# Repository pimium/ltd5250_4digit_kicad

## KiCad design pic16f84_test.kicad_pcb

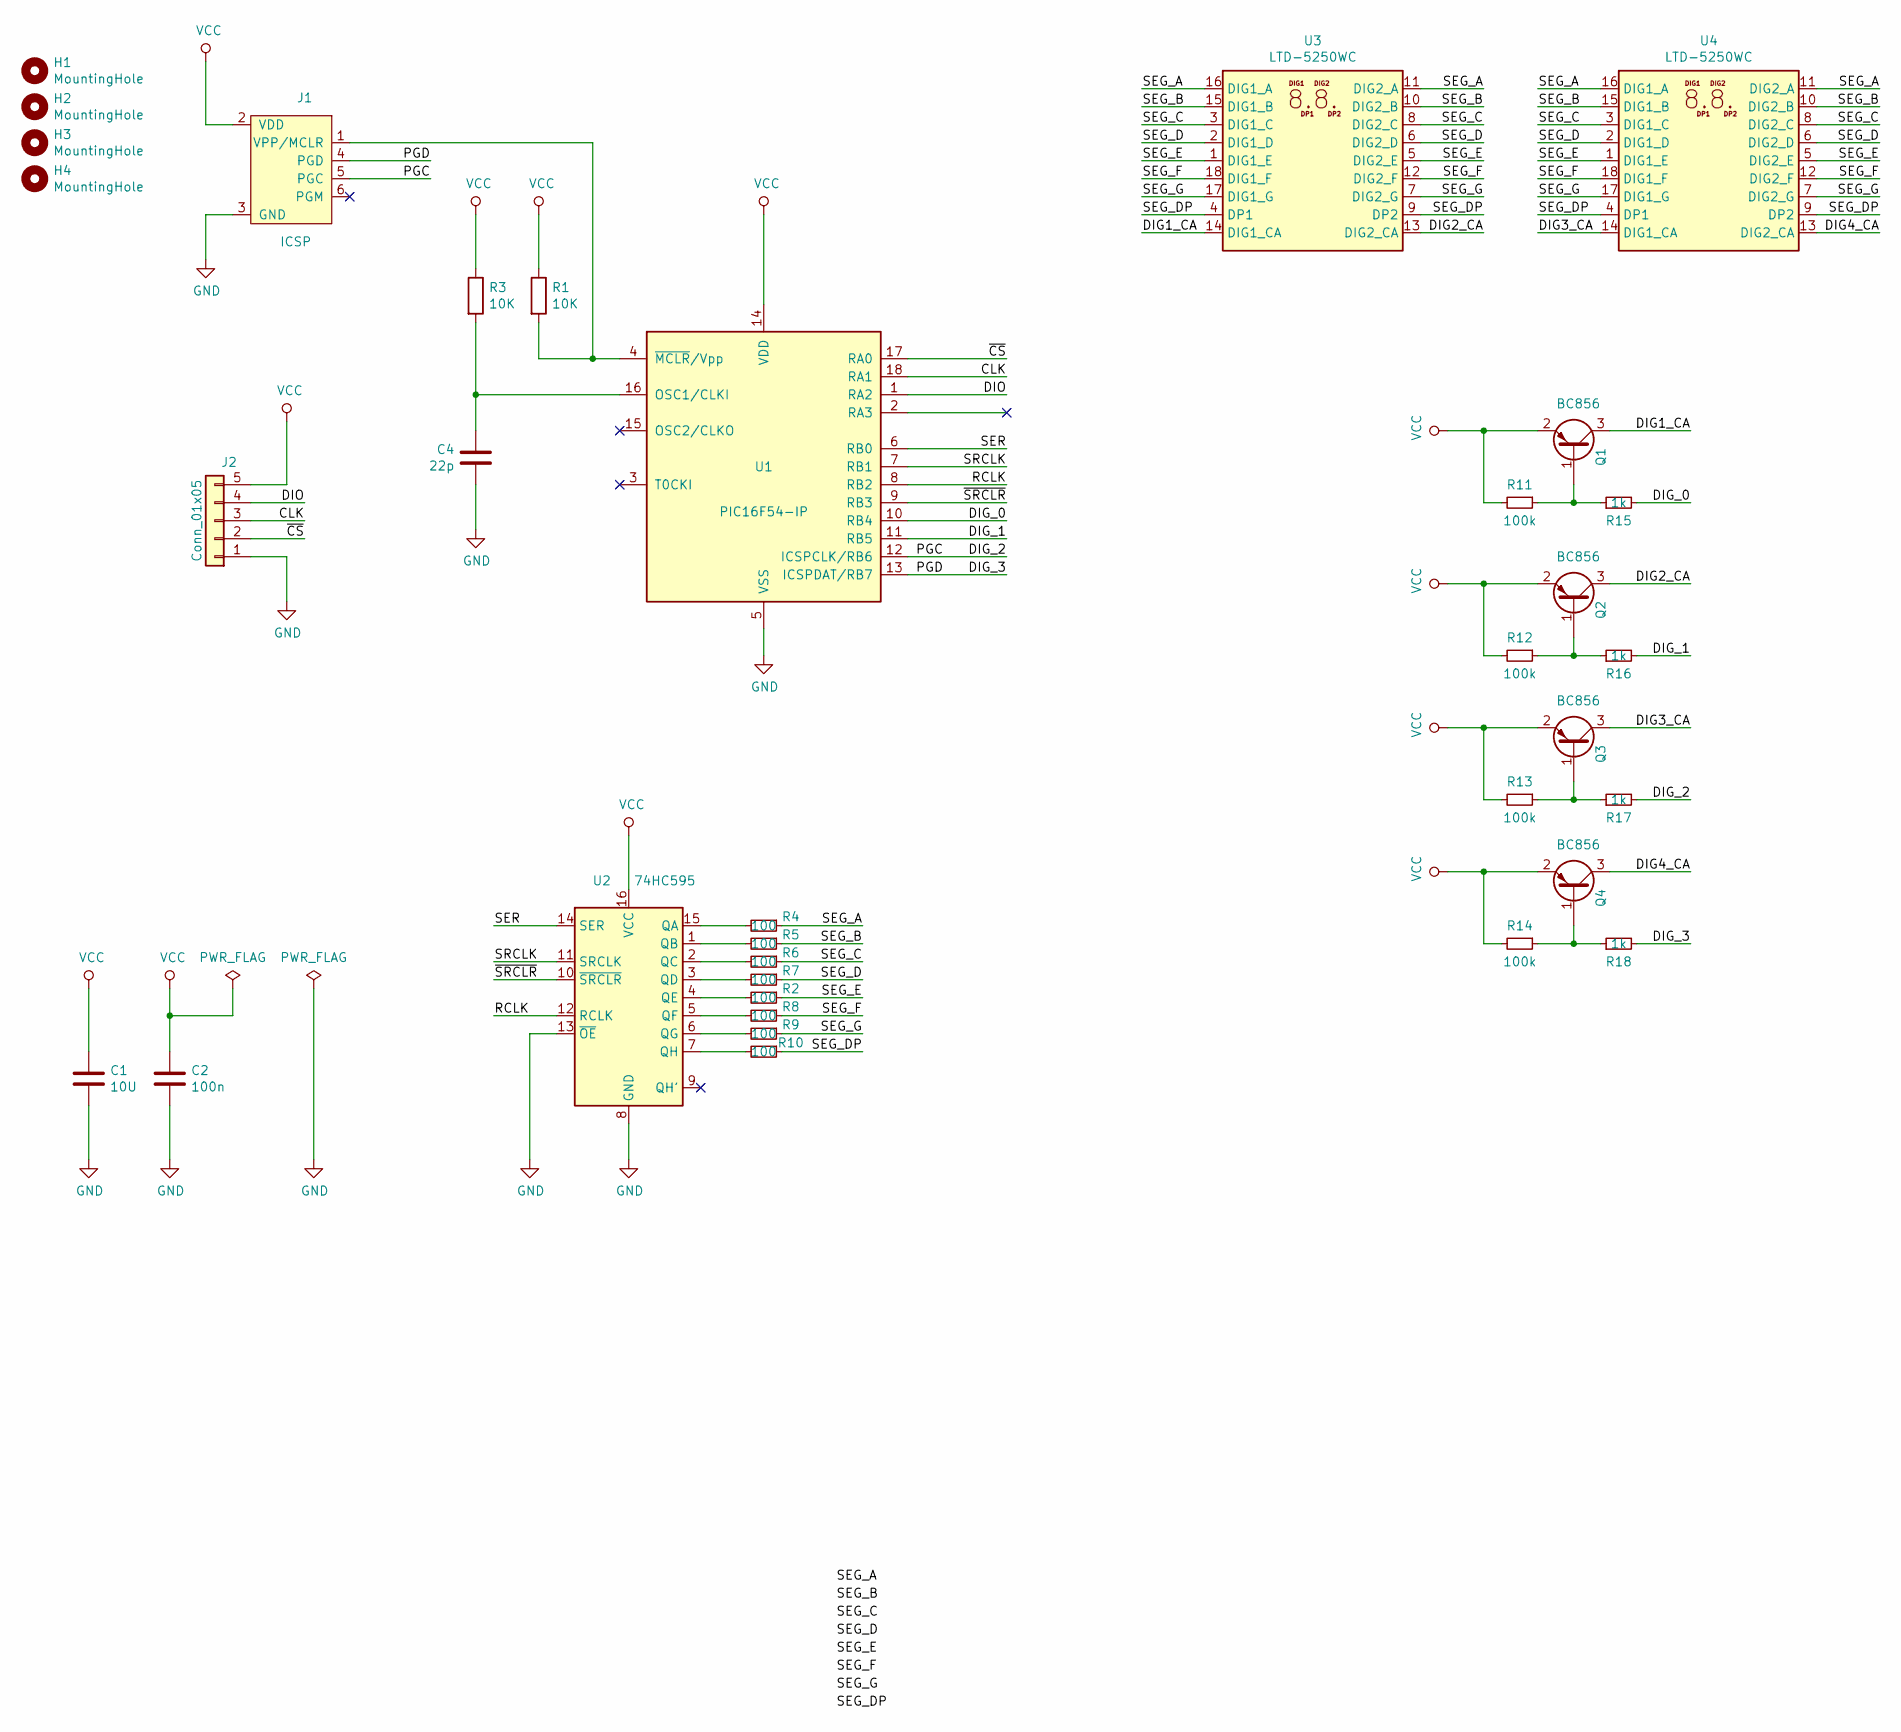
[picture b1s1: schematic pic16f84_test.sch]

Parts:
C1: 10U; C_0805_2012Metric_Pad1.15x1.40mm_HandSolder
C2: 100n; C_0805_2012Metric_Pad1.15x1.40mm_HandSolder
C4: 22p; C_0805_2012Metric_Pad1.15x1.40mm_HandSolder
H1, H2, H3, H4: MountingHole; MountingHole_3.2mm_M2
J1: ICSP; PinHeader_1x06_P2.54mm_Vertical
J2: Conn_01x05; PinHeader_1x05_P2.54mm_Vertical
Q1, Q2, Q3, Q4: BC856; SOT-23
R1, R3: 10K; R_0603_1608Metric_Pad1.05x0.95mm_HandSolder
R2, R4, R5, R6, R7, R8, R9, R10: 100; R_0603_1608Metric_Pad1.05x0.95mm_HandSolder
R11, R12, R13, R14: 100k; R_0603_1608Metric_Pad1.05x0.95mm_HandSolder
R15, R16, R17, R18: 1k; R_0603_1608Metric_Pad1.05x0.95mm_HandSolder
U1: PIC16F54-IP; SOP-18_7.0x12.5mm_P1.27mm
U2: 74HC595; SOIC-16_3.9x9.9mm_P1.27mm
U3, U4: LTD-5250WC; DA56-11CGKWA

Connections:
/CLK: J2.3, U1.18 (RA1)
/DIG1_CA: Q1.3 (C), U3.14 (DIG1_CA)
/DIG2_CA: Q2.3 (C), U3.13 (DIG2_CA)
/DIG3_CA: Q3.3 (C), U4.14 (DIG1_CA)
/DIG4_CA: Q4.3 (C), U4.13 (DIG2_CA)
/DIG_0: R15.2, U1.10 (RB4)
/DIG_1: R16.2, U1.11 (RB5)
/DIG_2: J1.5 (PGC), R17.2, U1.12 (ICSPCLK/RB6)
/DIG_3: J1.4 (PGD), R18.2, U1.13 (ICSPDAT/RB7)
/DIO: J2.4, U1.1 (RA2)
/RCLK: U1.8 (RB2), U2.12 (RCLK)
/SEG_A: R4.1, U3.11 (DIG2_A), U3.16 (DIG1_A), U4.11 (DIG2_A), U4.16 (DIG1_A)
/SEG_B: R5.1, U3.10 (DIG2_B), U3.15 (DIG1_B), U4.10 (DIG2_B), U4.15 (DIG1_B)
/SEG_C: R6.1, U3.3 (DIG1_C), U3.8 (DIG2_C), U4.3 (DIG1_C), U4.8 (DIG2_C)
/SEG_D: R7.1, U3.2 (DIG1_D), U3.6 (DIG2_D), U4.2 (DIG1_D), U4.6 (DIG2_D)
/SEG_DP: R10.1, U3.4 (DP1), U3.9 (DP2), U4.4 (DP1), U4.9 (DP2)
/SEG_E: R2.1, U3.1 (DIG1_E), U3.5 (DIG2_E), U4.1 (DIG1_E), U4.5 (DIG2_E)
/SEG_F: R8.1, U3.12 (DIG2_F), U3.18 (DIG1_F), U4.12 (DIG2_F), U4.18 (DIG1_F)
/SEG_G: R9.1, U3.7 (DIG2_G), U3.17 (DIG1_G), U4.7 (DIG2_G), U4.17 (DIG1_G)
/SER: U1.6 (RB0), U2.14 (SER)
/SRCLK: U1.7 (RB1), U2.11 (SRCLK)
/~CS: J2.2, U1.17 (RA0)
/~SRCLR: U1.9 (RB3), U2.10 (~SRCLR)
GND: C1.2, C2.2, C4.2, J1.3 (GND), J2.1, U1.5 (VSS), U2.8 (GND), U2.13 (~OE)
unnamed: C4.1, R3.2, U1.16 (OSC1/CLKI)
unnamed: J1.1 (VPP/MCLR), R1.2, U1.4 (~MCLR~/Vpp)
unnamed: Q1.1 (B), R11.1, R15.1
unnamed: Q2.1 (B), R12.1, R16.1
unnamed: Q3.1 (B), R13.1, R17.1
unnamed: Q4.1 (B), R14.1, R18.1
unnamed: R2.2, U2.4 (QE)
unnamed: R4.2, U2.15 (QA)
unnamed: R5.2, U2.1 (QB)
unnamed: R6.2, U2.2 (QC)
unnamed: R7.2, U2.3 (QD)
unnamed: R8.2, U2.5 (QF)
unnamed: R9.2, U2.6 (QG)
unnamed: R10.2, U2.7 (QH)
VCC: C1.1, C2.1, J1.2 (VDD), J2.5, Q1.2 (E), Q2.2 (E), Q3.2 (E), Q4.2 (E), R1.1, R3.1, R11.2, R12.2, R13.2, R14.2, U1.14 (VDD), U2.16 (VCC)

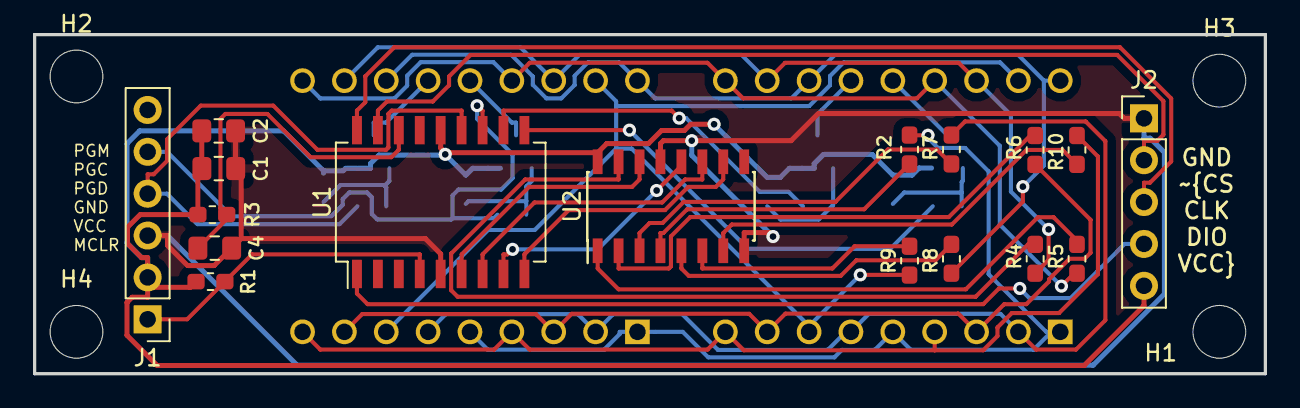
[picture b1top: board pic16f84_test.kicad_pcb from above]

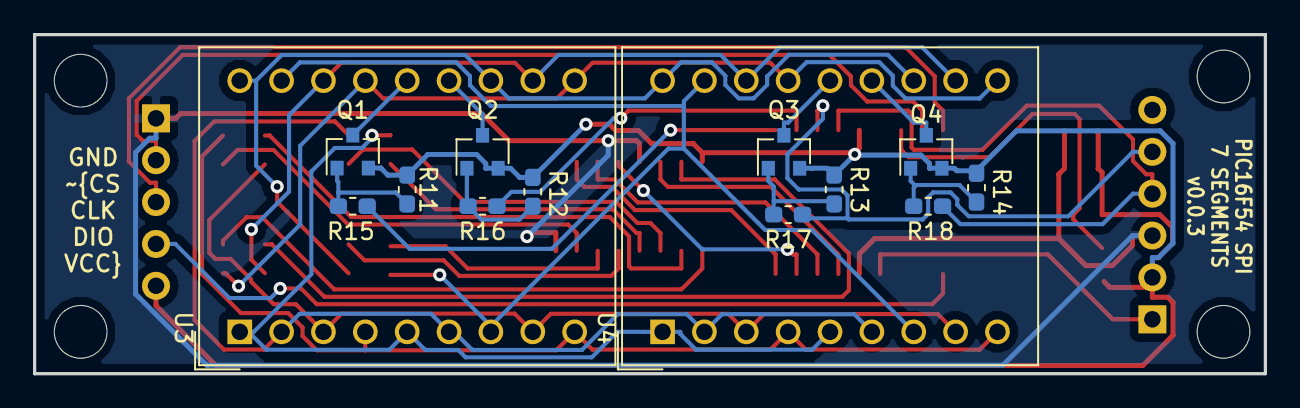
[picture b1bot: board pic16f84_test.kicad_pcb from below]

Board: 2 copper layers, 74.7 x 20.6 mm, 35 parts (14 on the bottom side), 39 nets.
